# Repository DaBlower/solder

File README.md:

# Duckchain
A fun light-up-in-the-dark pcb shaped like a duck! You can also use it as a keytag for decoration.

## Schematic

## PCB

## BOM
* 1 Battery holder
* 1 NPN Transistor
* 1 LED
* 2 Potentiometer
* 1 Photoresistor
* 2 Resistors

Made by ```@obob``` on slack for https://solder.hackclub.com/!

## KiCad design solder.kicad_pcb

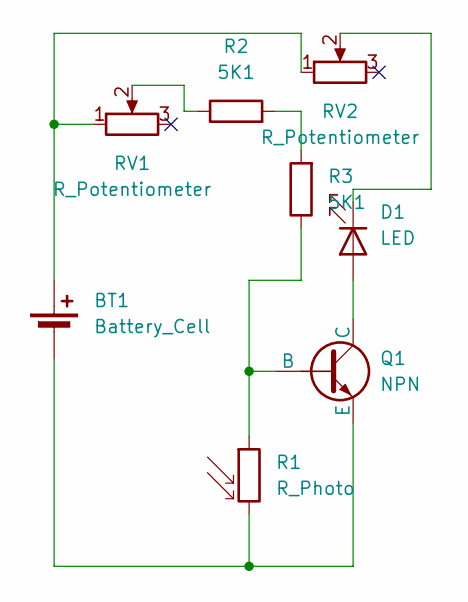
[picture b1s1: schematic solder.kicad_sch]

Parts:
BT1: Battery_Cell; BatteryHolder_Keystone_3034_1x20mm
D1: LED; LED_D5.0mm
Q1: NPN; TO-92L_HandSolder
R1: R_Photo; R_LDR_5.1x4.3mm_P3.4mm_Vertical
R2, R3: 5K1; R_Axial_DIN0207_L6.3mm_D2.5mm_P7.62mm_Horizontal
RV1, RV2: R_Potentiometer; Potentiometer_Vishay_T73YP_Vertical

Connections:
unnamed: BT1.1 (+), RV1.1, RV2.1
unnamed: BT1.2 (-), Q1.3 (E), R1.2
unnamed: D1.2 (A), Q1.1 (C)
unnamed: D1.1 (K), RV2.2
unnamed: Q1.2 (B), R1.1, R3.1
unnamed: R2.1, RV1.2
unnamed: R2.2, R3.2

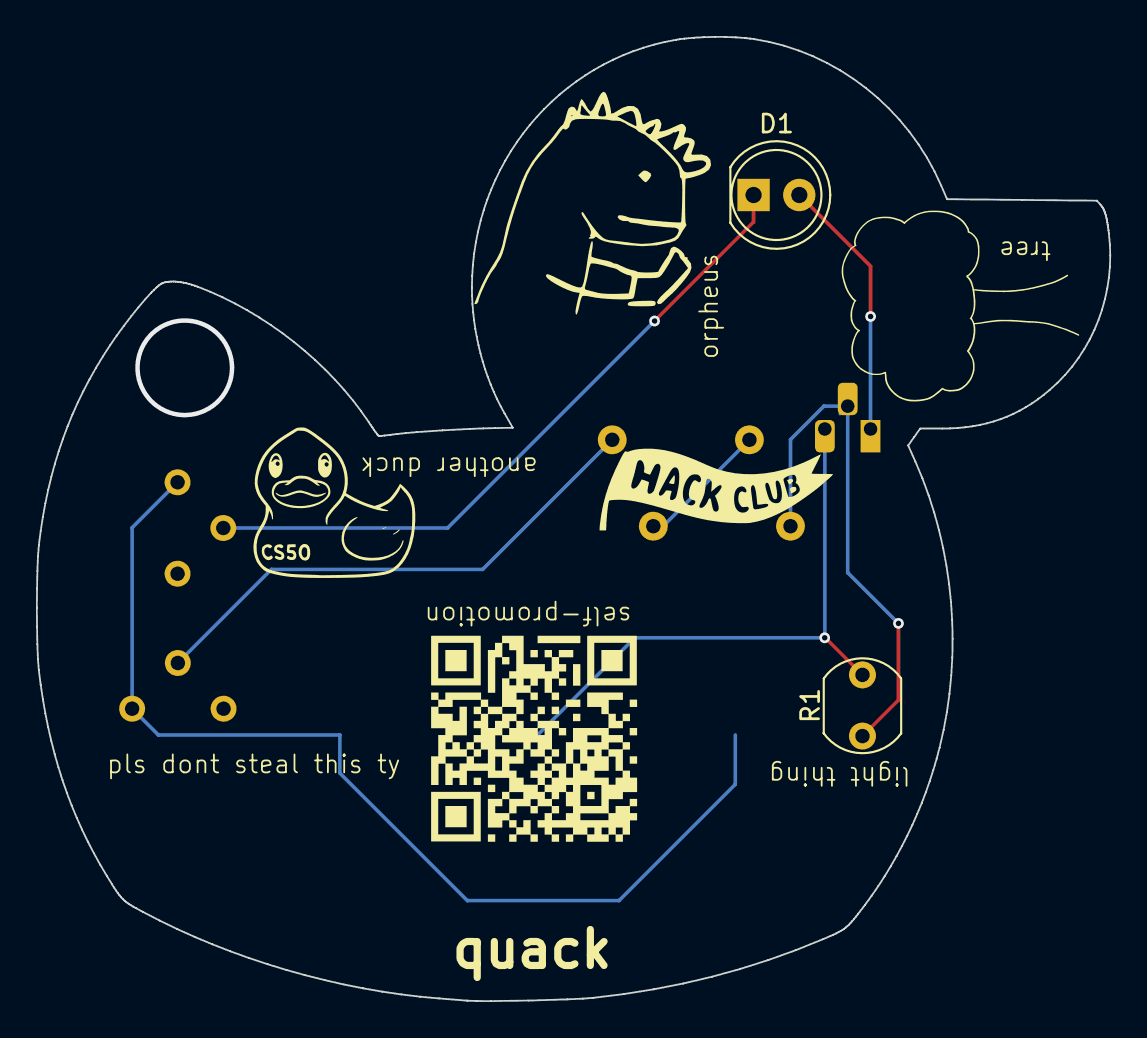
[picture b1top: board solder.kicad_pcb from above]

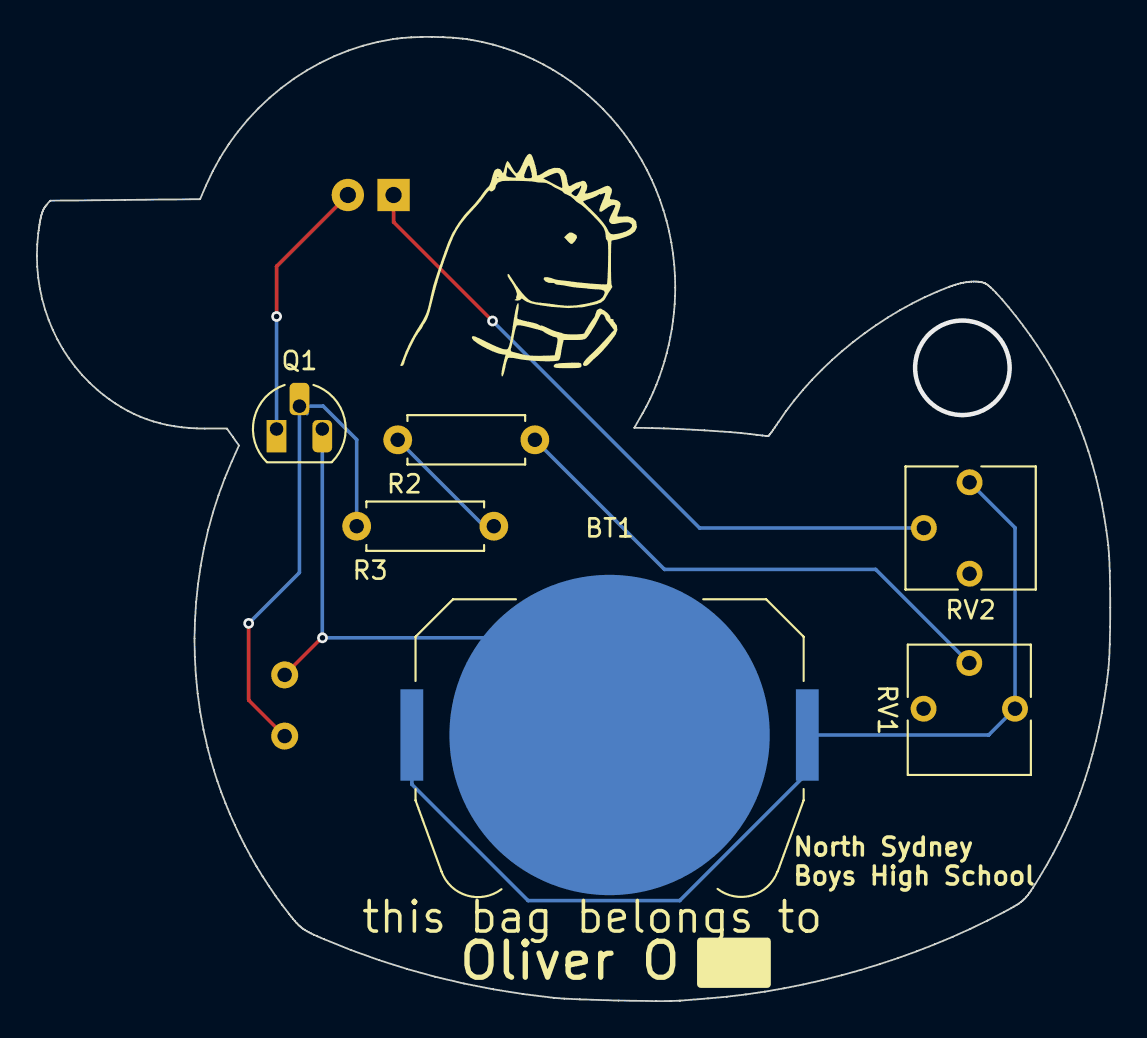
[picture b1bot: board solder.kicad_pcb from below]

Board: 2 copper layers, 59.6 x 53.6 mm, 8 parts (6 on the bottom side), 7 nets.

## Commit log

2025-06-21 finish schematic
2025-06-22 PCB Draft 1
2025-06-22 add keychain hole
2025-06-22 add pcb and schema screenshots
2025-06-22 add 3d image
2025-06-23 add production files
2025-06-24 add resistor
2025-06-24 remove unnecessary gerbers
2025-06-24 update images and pcb
2025-06-24 drill settings
2025-06-24 Update BOM
2025-06-24 update silkscreen
